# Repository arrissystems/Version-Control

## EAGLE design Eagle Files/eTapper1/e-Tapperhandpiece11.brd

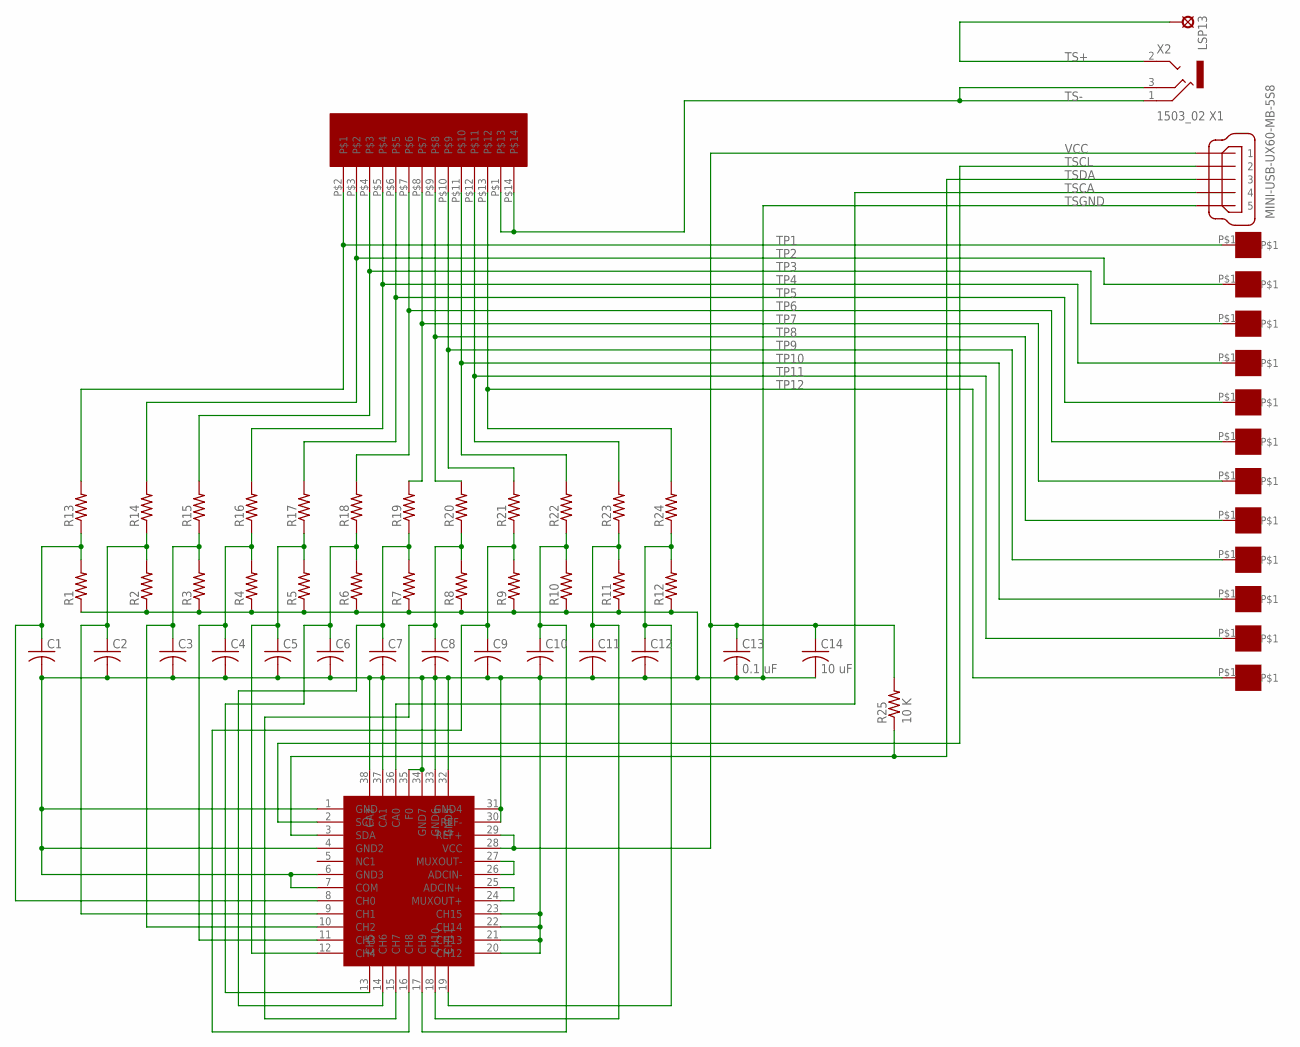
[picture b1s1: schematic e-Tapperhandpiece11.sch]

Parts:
C1, C2, C3, C4, C5, C6, C7, C8, C9, C10, C11, C12: C-USC0603; C0603
C13: 0.1 uF; C0603
C14: 10 uF; C0805
LSP13: SE11
R1, R2, R3, R4, R5, R6, R7, R8, R9, R10, R11, R12, R13, R14, R15, R16, R17, R18, R19, R20, R21, R22, R23, R24: R-US_R0402; R0402
R25: 10 K; R0402
TSP1, TSP2, TSP3, TSP4, TSP5, TSP6, TSP7, TSP8, TSP9, TSP10, TSP11, TSP12: ET1
U$1: LTC2497; QFN38-5X7
U$2: SS112D01
X1: MINI-USB-UX60-MB-5S8; UX60-MB-5S8
X2: 1503_02

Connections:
unnamed: C9.1, R9.2, R21.1, U$1.16 (CH8)
unnamed: U$1.26 (ADCIN-), U$1.27 (MUXOUT-)
unnamed: U$1.24 (MUXOUT+), U$1.25 (ADCIN+)
unnamed: C12.1, R12.2, R24.1, U$1.19 (CH11)
unnamed: C4.1, R4.2, R16.1, U$1.11 (CH3)
unnamed: C10.1, R10.2, R22.1, U$1.17 (CH9)
unnamed: C8.1, R8.2, R20.1, U$1.15 (CH7)
unnamed: C5.1, R5.2, R17.1, U$1.12 (CH4)
unnamed: C6.1, R6.2, R18.1, U$1.13 (CH5)
unnamed: C7.1, R7.2, R19.1, U$1.14 (CH6)
unnamed: C3.1, R3.2, R15.1, U$1.10 (CH2)
unnamed: C2.1, R2.2, R14.1, U$1.9 (CH1)
unnamed: C11.1, R11.2, R23.1, U$1.18 (CH10)
unnamed: C1.1, R1.2, R13.1, U$1.8 (CH0)
TP1: R13.2, TSP1.P$1, U$2.P$2
TP2: R14.2, TSP2.P$1, U$2.P$3
TP3: R15.2, TSP3.P$1, U$2.P$4
TP4: R16.2, TSP4.P$1, U$2.P$5
TP5: R17.2, TSP5.P$1, U$2.P$6
TP6: R18.2, TSP6.P$1, U$2.P$7
TP7: R19.2, TSP7.P$1, U$2.P$8
TP8: R20.2, TSP8.P$1, U$2.P$9
TP9: R21.2, TSP9.P$1, U$2.P$10
TP10: R22.2, TSP10.P$1, U$2.P$11
TP11: R23.2, TSP11.P$1, U$2.P$12
TP12: R24.2, TSP12.P$1, U$2.P$13
TS+: LSP13.MP, X2.2
TS-: U$2.P$1, U$2.P$14, X2.1, X2.3
TSCA: U$1.36 (CA0), X1.4
TSCL: U$1.2 (SCL), X1.2
TSDA: R25.1, U$1.3 (SDA), X1.3
TSGND: C1.2, C2.2, C3.2, C4.2, C5.2, C6.2, C7.2, C8.2, C9.2, C10.2, C11.2, C12.2, C13.2, C14.2, R1.1, R2.1, R3.1, R4.1, R5.1, R6.1, R7.1, R8.1, R9.1, R10.1, R11.1, R12.1, U$1.1 (GND), U$1.4 (GND2), U$1.6 (GND3), U$1.7 (COM), U$1.20 (CH12), U$1.21 (CH13), U$1.22 (CH14), U$1.23 (CH15), U$1.30 (REF-), U$1.31 (GND4), U$1.32 (GND5), U$1.33 (GND6), U$1.34 (GND7), U$1.35 (F0), U$1.37 (CA1), U$1.38 (CA2), X1.5
VCC: C13.1, C14.1, R25.2, U$1.28 (VCC), U$1.29 (REF+), X1.1

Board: 2 copper layers, 56 parts (0 on the bottom side), 33 nets, no tracks yet.

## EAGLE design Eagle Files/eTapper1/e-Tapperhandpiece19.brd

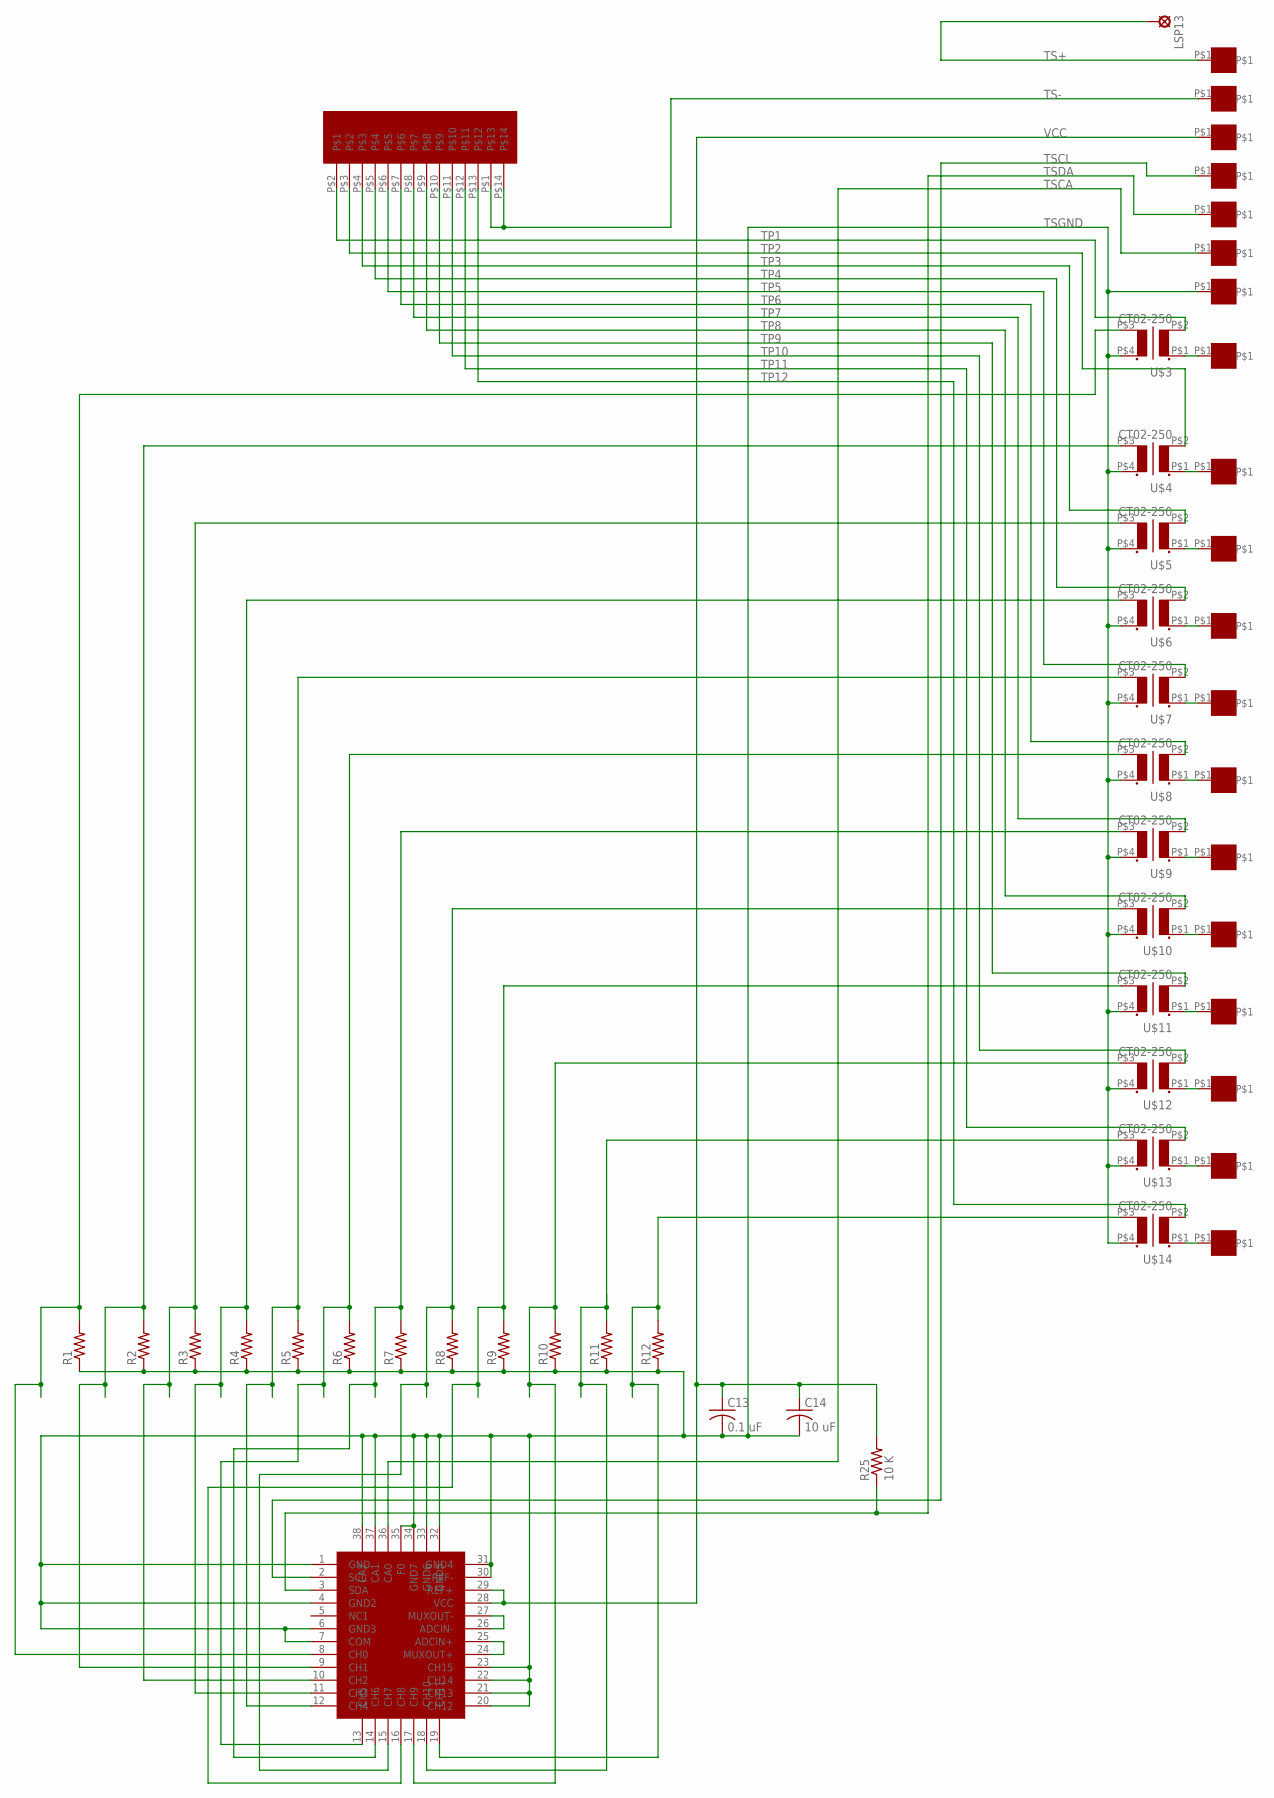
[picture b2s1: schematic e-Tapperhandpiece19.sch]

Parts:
C13: 0.1 uF; C0603
C14: 10 uF; C0805
LSP13: SE11
R1, R2, R3, R4, R5, R6, R7, R8, R9, R10, R11, R12: R-US_R0402; R0402
R25: 10 K; R0402
TSP1, TSP2, TSP3, TSP4, TSP5, TSP6, TSP7, TSP8, TSP9, TSP10, TSP11, TSP12, TSP13, TSP14, TSP15, TSP16, TSP17, TSP18, TSP19: ET1
U$1: LTC2497; QFN38-5X7
U$2: SS112D01
U$3, U$4, U$5, U$6, U$7, U$8, U$9, U$10, U$11, U$12, U$13, U$14: CT02-250

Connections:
unnamed: R9.2, U$1.16 (CH8), U$11.P$3 (S2)
unnamed: U$1.26 (ADCIN-), U$1.27 (MUXOUT-)
unnamed: U$1.24 (MUXOUT+), U$1.25 (ADCIN+)
unnamed: TSP1.P$1, U$3.P$1 (P1)
unnamed: R12.2, U$1.19 (CH11), U$14.P$3 (S2)
unnamed: TSP2.P$1, U$4.P$1 (P1)
unnamed: R4.2, U$1.11 (CH3), U$6.P$3 (S2)
unnamed: R10.2, U$1.17 (CH9), U$12.P$3 (S2)
unnamed: R8.2, U$1.15 (CH7), U$10.P$3 (S2)
unnamed: TSP3.P$1, U$5.P$1 (P1)
unnamed: TSP4.P$1, U$6.P$1 (P1)
unnamed: TSP5.P$1, U$7.P$1 (P1)
unnamed: TSP6.P$1, U$8.P$1 (P1)
unnamed: TSP7.P$1, U$9.P$1 (P1)
unnamed: TSP8.P$1, U$10.P$1 (P1)
unnamed: TSP9.P$1, U$11.P$1 (P1)
unnamed: TSP10.P$1, U$12.P$1 (P1)
unnamed: R5.2, U$1.12 (CH4), U$7.P$3 (S2)
unnamed: R6.2, U$1.13 (CH5), U$8.P$3 (S2)
unnamed: R7.2, U$1.14 (CH6), U$9.P$3 (S2)
unnamed: TSP11.P$1, U$13.P$1 (P1)
unnamed: R3.2, U$1.10 (CH2), U$5.P$3 (S2)
unnamed: R2.2, U$1.9 (CH1), U$4.P$3 (S2)
unnamed: R11.2, U$1.18 (CH10), U$13.P$3 (S2)
unnamed: R1.2, U$1.8 (CH0), U$3.P$3 (S2)
unnamed: TSP12.P$1, U$14.P$1 (P1)
TP1: U$2.P$2, U$3.P$2 (P2)
TP2: U$2.P$3, U$4.P$2 (P2)
TP3: U$2.P$4, U$5.P$2 (P2)
TP4: U$2.P$5, U$6.P$2 (P2)
TP5: U$2.P$6, U$7.P$2 (P2)
TP6: U$2.P$7, U$8.P$2 (P2)
TP7: U$2.P$8, U$9.P$2 (P2)
TP8: U$2.P$9, U$10.P$2 (P2)
TP9: U$2.P$10, U$11.P$2 (P2)
TP10: U$2.P$11, U$12.P$2 (P2)
TP11: U$2.P$12, U$13.P$2 (P2)
TP12: U$2.P$13, U$14.P$2 (P2)
TS+: LSP13.MP, TSP13.P$1
TS-: TSP14.P$1, U$2.P$1, U$2.P$14
TSCA: TSP18.P$1, U$1.36 (CA0)
TSCL: TSP16.P$1, U$1.2 (SCL)
TSDA: R25.1, TSP17.P$1, U$1.3 (SDA)
TSGND: C13.2, C14.2, R1.1, R2.1, R3.1, R4.1, R5.1, R6.1, R7.1, R8.1, R9.1, R10.1, R11.1, R12.1, TSP19.P$1, U$1.1 (GND), U$1.4 (GND2), U$1.6 (GND3), U$1.7 (COM), U$1.20 (CH12), U$1.21 (CH13), U$1.22 (CH14), U$1.23 (CH15), U$1.30 (REF-), U$1.31 (GND4), U$1.32 (GND5), U$1.33 (GND6), U$1.34 (GND7), U$1.35 (F0), U$1.37 (CA1), U$1.38 (CA2), U$3.P$4 (S1), U$4.P$4 (S1), U$5.P$4 (S1), U$6.P$4 (S1), U$7.P$4 (S1), U$8.P$4 (S1), U$9.P$4 (S1), U$10.P$4 (S1), U$11.P$4 (S1), U$12.P$4 (S1), U$13.P$4 (S1), U$14.P$4 (S1)
VCC: C13.1, C14.1, R25.2, TSP15.P$1, U$1.28 (VCC), U$1.29 (REF+)

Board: 2 copper layers, 49 parts (0 on the bottom side), 45 nets, no tracks yet.
